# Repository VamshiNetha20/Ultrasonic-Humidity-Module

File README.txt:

Smart Humidifier Code - ATmega328P
==================================

Author: G. Vamshi Krishna

This code controls an ultrasonic humidifier using an ATmega328P microcontroller.
The system accepts control input from either a push button or an HC-05 Bluetooth module and provides visual feedback using a status LED.

Features:
---------
- Push button toggles humidifier ON/OFF (connected to PD2, INT0)
- Bluetooth commands '1' and '0' received via HC-05 control ON/OFF (PD0/PD1)
- Status LED indicates active state (ON = LED ON)
- Uses interrupts for both external input and serial reception

Pin Connections:
----------------
- PD2 (INT0)   → Push Button Input
- PD3          → MOSFET Gate (controls humidifier)
- PD4          → Status LED
- PD0 (RXD)    ← HC-05 TX
- PD1 (TXD)    → HC-05 RX (via 1k resistor)

Flashing Instructions:
----------------------
- Use a USBasp or Arduino-as-ISP via the 6-pin ISP header
- Compile and flash with AVR-GCC or Arduino IDE (as C sketch)

Note:
-----
- No separate UART header is used; all serial communication is handled exclusively by HC-05.

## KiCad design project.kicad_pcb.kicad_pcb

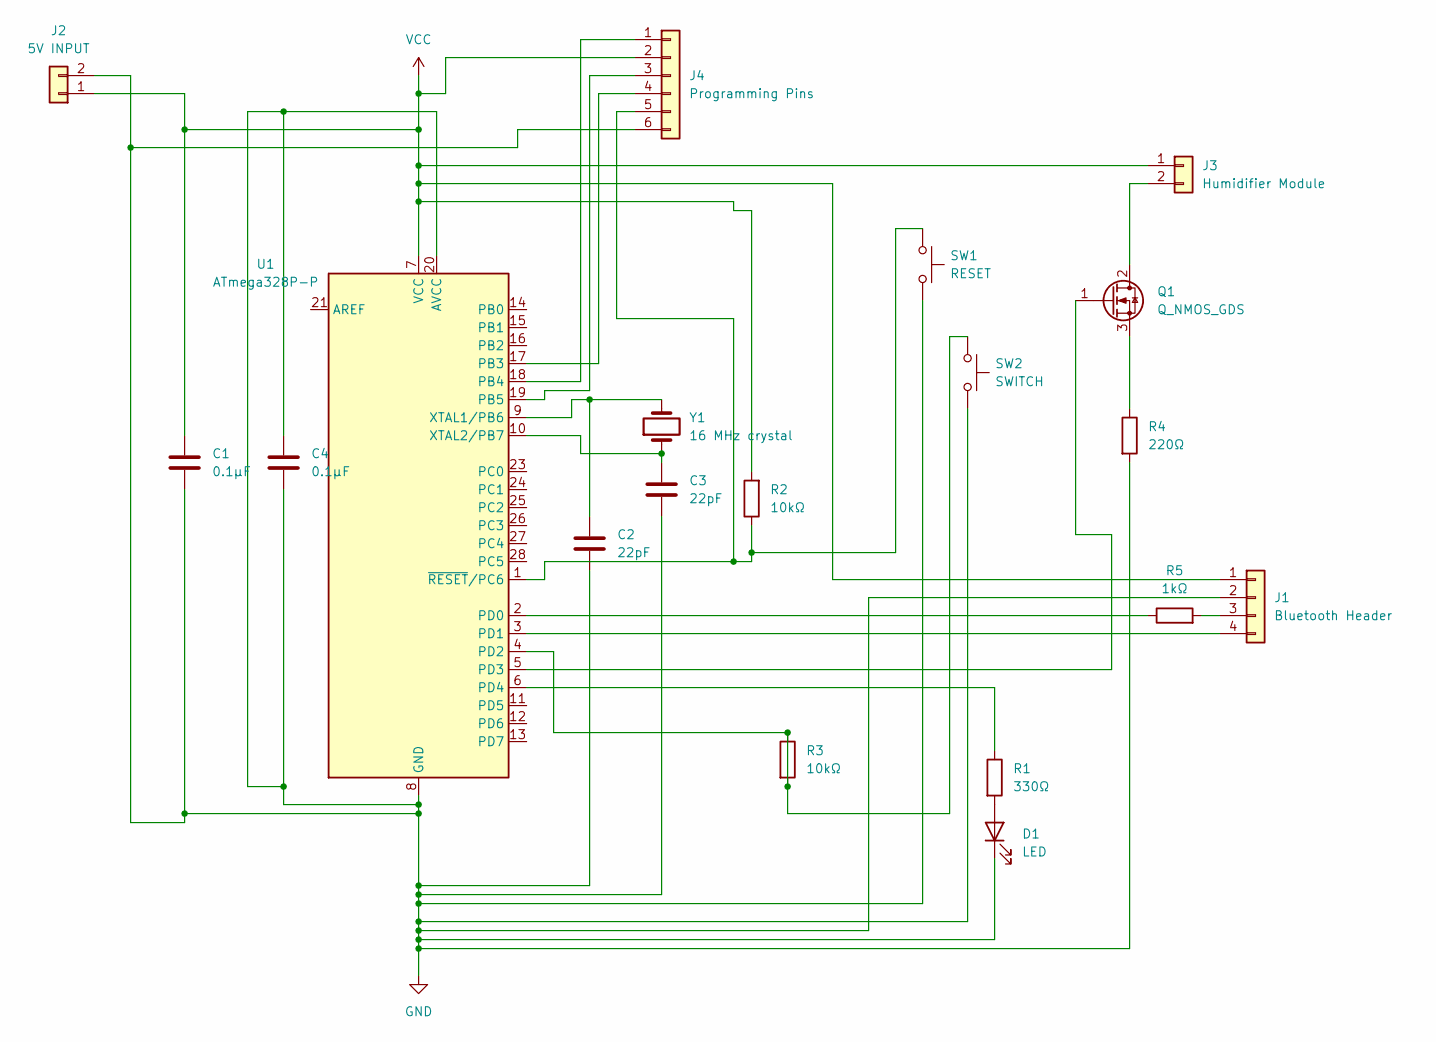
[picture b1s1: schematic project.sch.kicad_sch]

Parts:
C1, C4: 0.1µF; C_Disc_D5.0mm_W2.5mm_P5.00mm
C2: 22pF; C_Disc_D5.0mm_W2.5mm_P5.00mm
C3: 22pF; C_Disc_D5.0mm_W2.5mm_P2.50mm
D1: LED; LED_D5.0mm
J1: Bluetooth Header; PinHeader_1x04_P2.54mm_Vertical
J2: 5V INPUT; PinHeader_1x02_P2.54mm_Vertical
J3: Humidifier Module; PinHeader_1x02_P2.54mm_Vertical
J4: Programming Pins; PinHeader_1x06_P2.54mm_Vertical
Q1: Q_NMOS_GDS; TO-220-3_Vertical
R1: 330Ω; R_Axial_DIN0207_L6.3mm_D2.5mm_P7.62mm_Horizontal
R2, R3: 10kΩ; R_Axial_DIN0207_L6.3mm_D2.5mm_P7.62mm_Horizontal
R4: 220Ω; R_Axial_DIN0207_L6.3mm_D2.5mm_P7.62mm_Horizontal
R5: 1kΩ; R_Axial_DIN0207_L6.3mm_D2.5mm_P7.62mm_Horizontal
SW1: RESET; SW_PUSH_6mm_H5mm
SW2: SWITCH; SW_PUSH_6mm_H5mm
U1: ATmega328P-P; DIP-28_W7.62mm
Y1: 16 MHz crystal; Crystal_HC49-4H_Vertical

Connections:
GND: C1.2, C2.2, C3.2, C4.1, C4.2, D1.1 (K), J1.2, J2.2, J4.6, R4.2, SW1.2, SW2.2, U1.8 (GND), U1.20 (AVCC), U1.22 (GND)
unnamed: D1.2 (A), R1.2
unnamed: J1.3, R5.2
unnamed: J1.4, U1.3 (PD1)
unnamed: J3.2, Q1.2 (D)
unnamed: J4.1, U1.18 (PB4)
unnamed: J4.3, U1.19 (PB5)
unnamed: J4.4, U1.17 (PB3)
unnamed: J4.5, R2.1, SW1.1, U1.1 (~RESET/PC6)
unnamed: Q1.1 (G), U1.5 (PD3)
unnamed: Q1.3 (S), R4.1
unnamed: R5.1, U1.2 (PD0)
unnamed: R3.1, R3.2, SW2.1, U1.4 (PD2)
unnamed: R1.1, U1.6 (PD4)
unnamed: C2.1, U1.9 (XTAL1/PB6), Y1.2
unnamed: C3.1, U1.10 (XTAL2/PB7), Y1.1
VCC: C1.1, J1.1, J2.1, J3.1, J4.2, R2.2, U1.7 (VCC)

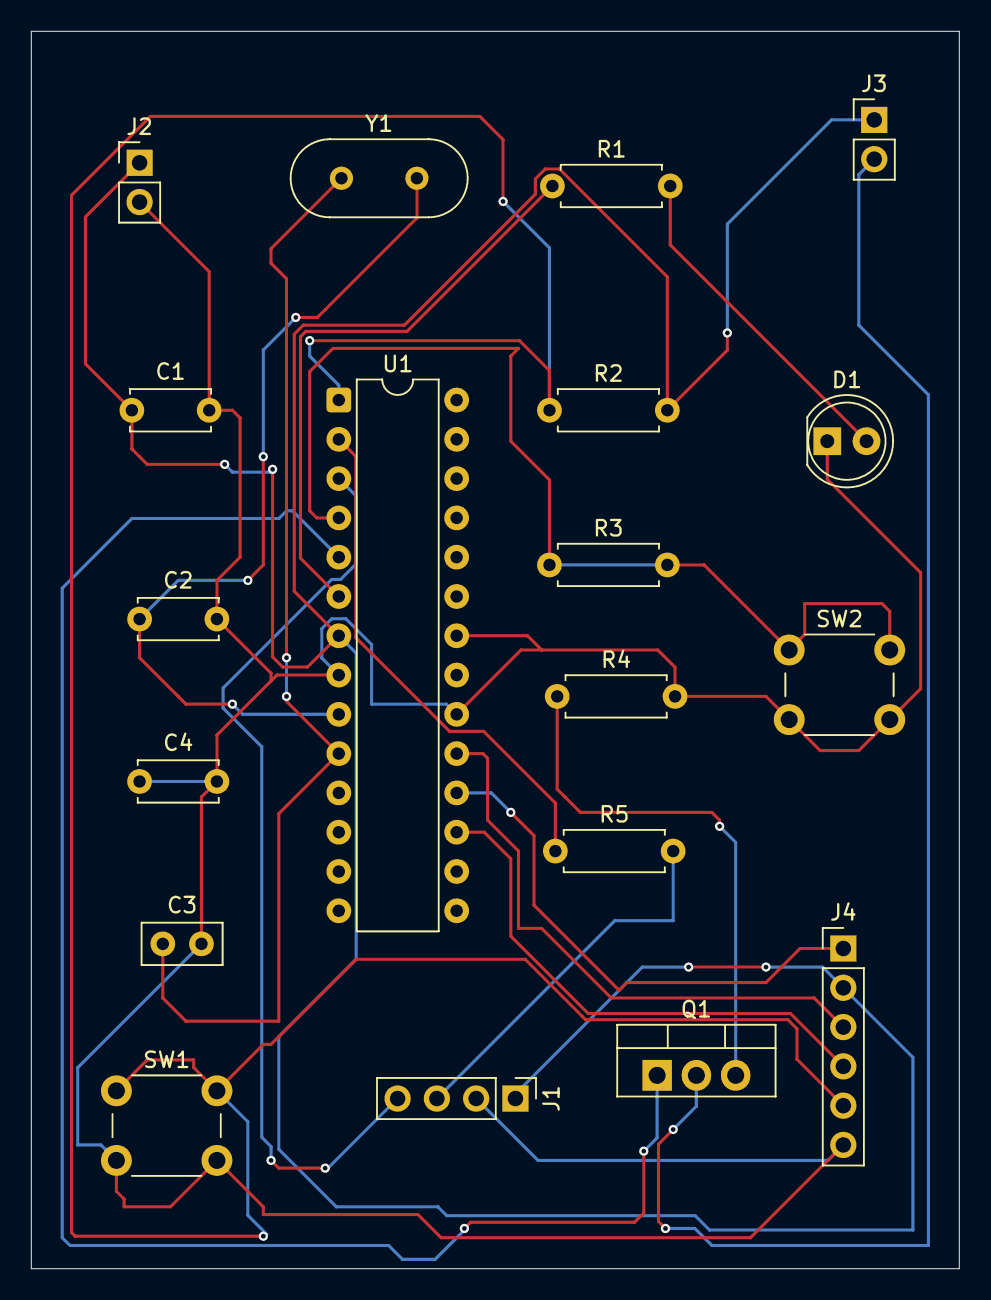
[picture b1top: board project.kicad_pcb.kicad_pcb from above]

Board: 2 copper layers, 60.0 x 80.0 mm, 19 parts (0 on the bottom side), 17 nets.
